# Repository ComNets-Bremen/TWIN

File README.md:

# TWIN Node/ Sprinkler Protocol

This Repository is for the Configuration and details regarding Firmware Distribution Protocol for the Backchannel of the __TWIN Nodes__.

## General Setup for TWIN Nodes

1. Clone the Repository on Raspberry Pi:

        git clone http://github.com/ComNets-Bremen/TWIN.git

2. Change directory:

        cd TWIN/

3. Run the `bootstrap.sh` with root privilege.

	    sudo ./bootstrap.sh

See [Wiki](https://github.com/ComNets-Bremen/TWIN/wiki/Setup) for details.

## Usage of Sprinkler Protocol

	$ python3 Sprinkler.py -h

	usage: Sprinkler.py [-h] [-V VERSION] [-b BLOCK] [-p PATH] [-f FILENAME]

	Data Dissemination in TWIN Back-Channel using Sprinkler Protocol

	optional arguments:
  	-h, --help            show this help message and exit
  	-V VERSION, --version VERSION
                        	Version Number
  	-b BLOCK, --block BLOCK
                        	Encoding Block Length
  	-p PATH, --path PATH  
  							Target Folder for Filename
  	-f FILENAME, --filename FILENAME
                        	Main File for Fountain

* `VERSION`: Integer value, describing the Version with which the __TWIN Node__ would start.

* `BLOCK`: Block Size for the LT-Encoded Block. The value should be less than __1500 Bytes__ (in order to avoid IPv6 fragmentation)

* `PATH`: this is the Path to the directory where the Firmware File lies or stored.

* `FILENAME`: the firmware file to be disseminated. This file should be a valid `.tar` file

### Default Values
All Default Values are taken from `Sprinkler/global_variables.py`. These values can be overriden according to applications.

## Description

__TWIN Nodes__ have __802.11 WLAN__ based Back-Channel for Uploading *Intel HEX (ihex)* files
for the __Zolertia Z1__ connected to Raspberry Pis via Isolation Boards.

This Library uses the concepts of __Multicasting over WLAN__. Here each __TWIN Node__ is using
*IPv6 Link-Local Addressing Scheme* and is a part of the Multicast Group `ff02::1`.

Firmware for each __TWIN__ consists of the following:

* A configuration file : `config.ini`

* `program1.ihex`

* `program2.ihex`
...so on.

The complete Firmware above is sent as a single `tar` file over the Back-Channel as, for example `data1.tar`.

## Further Information

This Project is supported with a detailed [Wiki](https://github.com/ComNets-Bremen/TWIN/wiki).

For further queries please [Contact Us at ComNets, Universität Bremen](https://github.com/ComNets-Bremen/TWIN/wiki/Contact-Details)

## License

This Project is issued under the __GNU GPLv3__ License

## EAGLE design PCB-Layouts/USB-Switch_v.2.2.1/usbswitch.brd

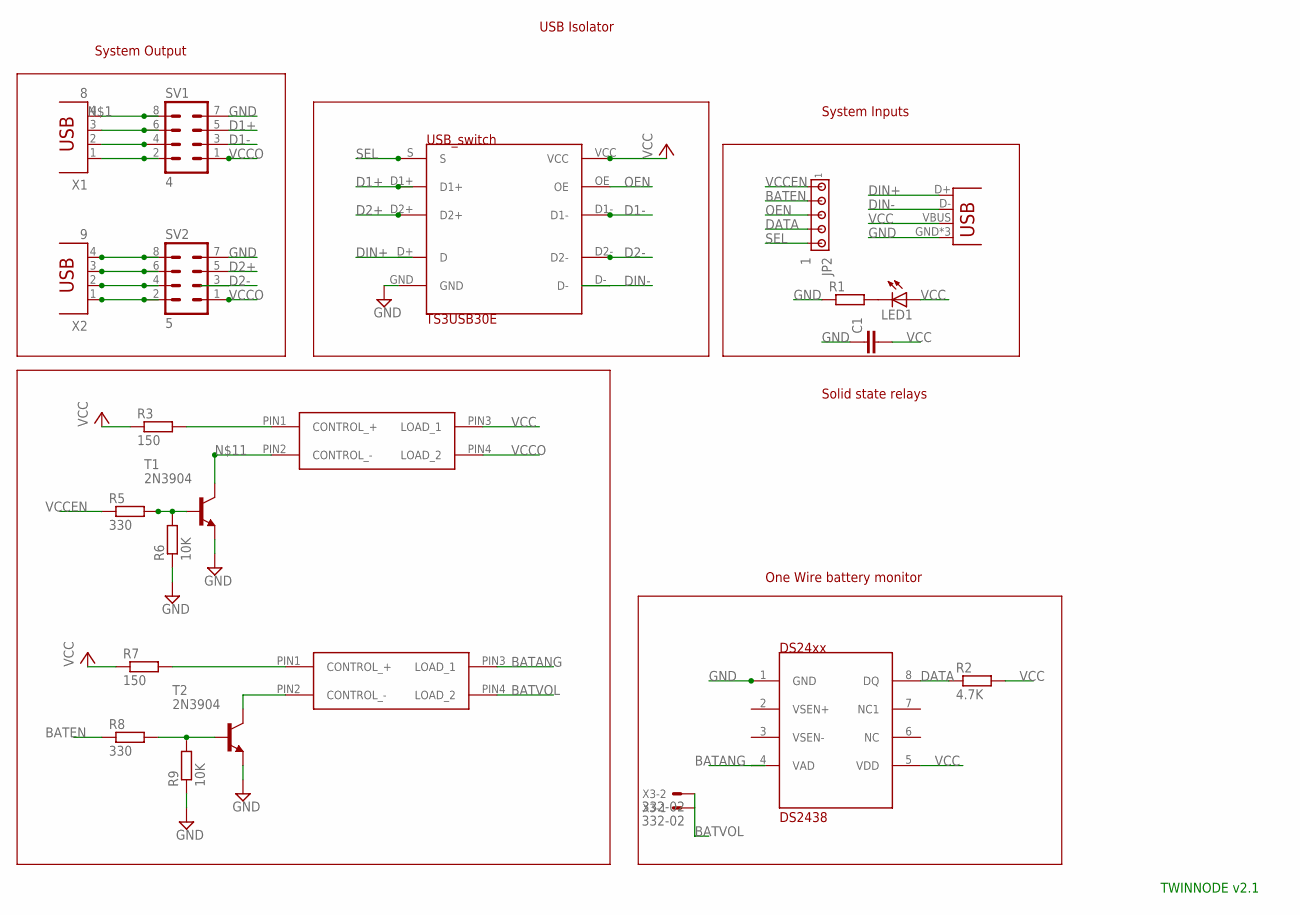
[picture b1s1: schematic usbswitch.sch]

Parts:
C1: C2.5/6; C2.5-6
JP1: USB-MICROB
JP2: 1; 10X05MTA
LED1: LED_ELD260; LED_LD260
R1: RR3216; R3216
R2: 4.7K; R3216
R3, R7: 150; R3216
R5, R8: 330; R3216
R6, R9: 10K; R3216
SV1: 4; MA04-2
SV2: 5; MA04-2
T1, T2: 2N3904; TO92
U$1: USB_SWITCH; PDSO-G10
U$2: DS2438; DS243PKG
U$3, U$4: OPTO-RELAY-CPC1017N; SOP-4
X1: 8; PN87520
X2: 9; PN87520
X3: 332-02

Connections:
BATANG: U$2.4 (VAD), U$3.PIN3 (LOAD_1)
BATEN: JP2.2, R8.1
BATVOL: U$3.PIN4 (LOAD_2), X3.1, X3.2
D1+: SV1.5, U$1.D1+
D1-: SV1.3, U$1.D1-
D2+: SV2.5, U$1.D2+
D2-: SV2.3, U$1.D2-
DATA: JP2.4, R2.1, U$2.8 (DQ)
DIN+: JP1.D+, U$1.D+ (D)
DIN-: JP1.D-, U$1.D-
GND: C1.1, JP1.GND, JP1.MT1 (GND), JP1.MT2 (GND), R1.1, R6.1, R9.1, SV1.7, SV2.7, T1.3 (E), T2.3 (E), U$1.GND, U$2.1 (GND)
unnamed: SV1.8, X1.4
unnamed: SV1.6, X1.3
unnamed: SV1.4, X1.2
unnamed: LED1.K (C), R1.2
unnamed: SV2.8, X2.4
unnamed: SV2.6, X2.3
unnamed: SV2.4, X2.2
unnamed: R5.2, R6.2, T1.2 (B)
unnamed: T1.1 (C), U$4.PIN2 (CONTROL_-)
unnamed: R3.2, U$4.PIN1 (CONTROL_+)
unnamed: R8.2, R9.2, T2.2 (B)
unnamed: T2.1 (C), U$3.PIN2 (CONTROL_-)
unnamed: R7.2, U$3.PIN1 (CONTROL_+)
unnamed: SV1.2, X1.1
unnamed: SV2.2, X2.1
OEN: JP2.3, U$1.OE
SEL: JP2.5, U$1.S
VCC: C1.2, JP1.VBUS, LED1.A, R2.2, R3.1, R7.1, U$1.VCC, U$2.5 (VDD), U$4.PIN3 (LOAD_1)
VCCEN: JP2.1, R5.1
VCCO: SV1.1, SV2.1, U$4.PIN4 (LOAD_2)

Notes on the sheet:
System Inputs
Solid state relays
USB Isolator
System Output
One Wire battery monitor
TWINNODE v2.1

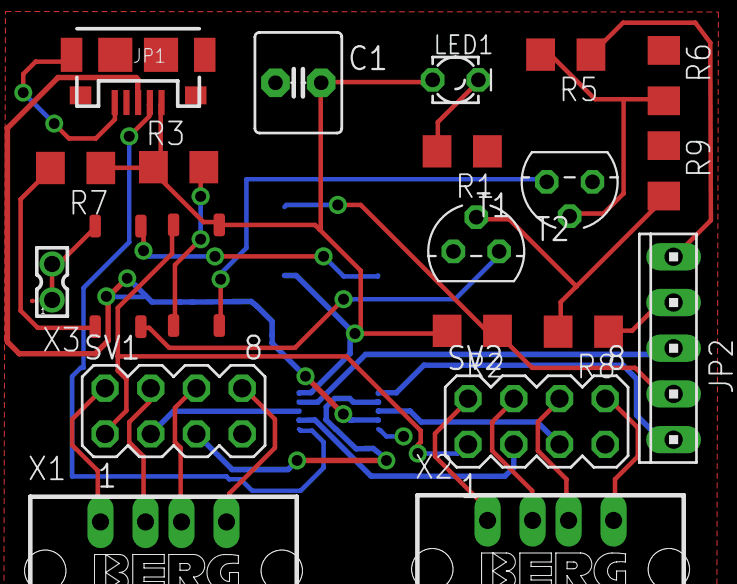
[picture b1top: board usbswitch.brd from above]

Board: 2 copper layers, 23 parts (1 on the bottom side), 31 nets.

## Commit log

2016-07-12 added the Images folder
2016-07-12 Added Image folders/floor plans
2016-07-12 added Overall plans
2016-09-02 CLEANUP
2016-09-02 Overview:v2.0
2016-09-02 Added License Tags w/ comments, OCDCompliant:v2.0
2016-09-02 added Argument explanation:v2.0
2016-09-03 added Scanning/Triggering Scripts:v2.0
2016-09-03 added data retrieval scripts:v2.0
2016-09-03 added newline for clean look:v2.0
2016-09-20 Changed exec mode, added suffix, added bslscript + license:v2.0
2016-09-20 changes to README v2.0
2016-09-20 minor change
2016-09-21 Change Global Variables acc. to Pi v2.0
2016-10-01 Added Feature: GPIO Access via HTTP Server v2.1
2016-10-01 window session (TMUX) for GPIO HTTP server: v2.1
2016-11-30 Add GPIO control via config file
2016-12-13 Fixed Bugs with createSession.sh
2016-12-13 Added a User-Friendly Bootstrap script
2016-12-14 Changed erroneous comment in interfaces file for bootstrap
2016-12-15 Made front README more clear, renamed ambiguous TWIN module with appropriate Sprinkler name
2016-12-15 A little bit more helpful first step in README.md
2016-12-15 Changed Module names and minor corrections for Bash scripts
2016-12-16 wrong parameter for Ping in bootstrap.sh solved
2016-12-28 Added TWIN Node Logo directory and in README
2016-12-28 Quick HotFix for README post logo addition
2017-01-26 Update: SS Relays, reduced size, uUSB design
2017-01-26 refactor: name discrepancy for filename
2017-01-27 adhoc network creation post bootstraping solved
2017-02-17 Refactor: PEP8 Compliant Code
2017-02-20 bootstrapping compatible with Pi2/3
2017-02-20 Bootstrapping with Pi2/3 v2.2.1
2017-03-21 fix spacing problem bash for suffix
2017-03-27 Add modules on boot and appropriate checks for internal/external chipsets
